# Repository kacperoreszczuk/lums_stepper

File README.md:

# lums_stepper
LUMS Stepper - universal 3-axis stepper motor controller. See lums_stepper.pdf for instructions and more information.

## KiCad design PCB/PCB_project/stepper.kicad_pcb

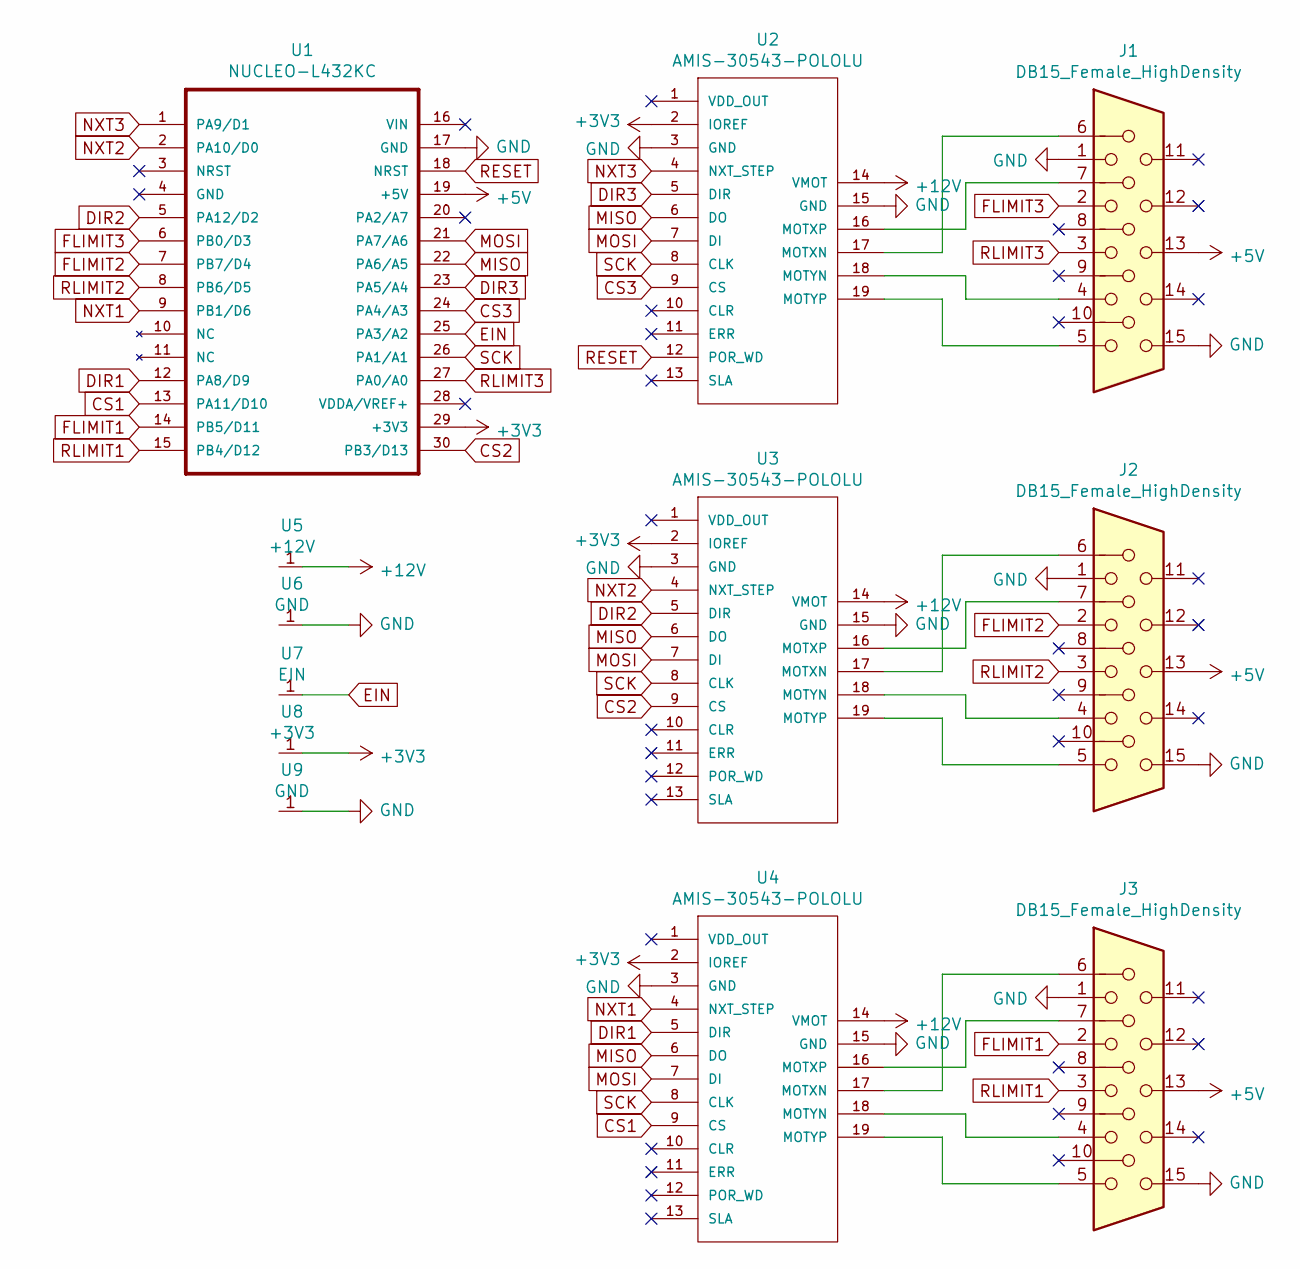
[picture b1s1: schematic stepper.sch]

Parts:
J1, J2, J3: DB15_Female_HighDensity; DSUB-15-HD_Male_Horizontal_Pitch2.29x2.54mm_EdgePinOffset9.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
U1: NUCLEO-L432KC
U2, U3, U4: AMIS-30543-POLOLU
U5: +12V; SolderWirePad_single_2mmDrill
U6: GND; SolderWirePad_single_2mmDrill
U7: EIN; TestPoint_Plated_Hole_D2.0mm
U8: +3V3; TestPoint_Plated_Hole_D2.0mm
U9: GND; TestPoint_Plated_Hole_D2.0mm

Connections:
+3V3: U1.29 (+3V3), U2.2 (IOREF), U3.2 (IOREF), U4.2 (IOREF), U8.1
+5V: J1.13, J2.13, J3.13, U1.19 (+5V)
+12V: U2.14 (VMOT), U3.14 (VMOT), U4.14 (VMOT), U5.1
CS1: U1.13 (PA11/D10), U4.9 (CS)
CS2: U1.30 (PB3/D13), U3.9 (CS)
CS3: U1.24 (PA4/A3), U2.9 (CS)
DIR1: U1.12 (PA8/D9), U4.5 (DIR)
DIR2: U1.5 (PA12/D2), U3.5 (DIR)
DIR3: U1.23 (PA5/A4), U2.5 (DIR)
EIN: U1.25 (PA3/A2), U7.1
FLIMIT1: J3.2, U1.14 (PB5/D11)
FLIMIT2: J2.2, U1.7 (PB7/D4)
FLIMIT3: J1.2, U1.6 (PB0/D3)
GND: J1.1, J1.15, J2.1, J2.15, J3.1, J3.15, U1.17 (GND), U2.3 (GND), U2.15 (GND), U3.3 (GND), U3.15 (GND), U4.3 (GND), U4.15 (GND), U6.1, U9.1
MISO: U1.22 (PA6/A5), U2.6 (DO), U3.6 (DO), U4.6 (DO)
MOSI: U1.21 (PA7/A6), U2.7 (DI), U3.7 (DI), U4.7 (DI)
NXT1: U1.9 (PB1/D6), U4.4 (NXT_STEP)
NXT2: U1.2 (PA10/D0), U3.4 (NXT_STEP)
NXT3: U1.1 (PA9/D1), U2.4 (NXT_STEP)
unnamed: J1.4, U2.18 (MOTYN)
unnamed: J1.5, U2.19 (MOTYP)
unnamed: J1.6, U2.17 (MOTXN)
unnamed: J1.7, U2.16 (MOTXP)
unnamed: J2.4, U3.18 (MOTYN)
unnamed: J2.5, U3.19 (MOTYP)
unnamed: J2.6, U3.17 (MOTXN)
unnamed: J2.7, U3.16 (MOTXP)
unnamed: J3.4, U4.18 (MOTYN)
unnamed: J3.5, U4.19 (MOTYP)
unnamed: J3.6, U4.17 (MOTXN)
unnamed: J3.7, U4.16 (MOTXP)
RESET: U1.18 (NRST), U2.12 (POR_WD)
RLIMIT1: J3.3, U1.15 (PB4/D12)
RLIMIT2: J2.3, U1.8 (PB6/D5)
RLIMIT3: J1.3, U1.27 (PA0/A0)
SCK: U1.26 (PA1/A1), U2.8 (CLK), U3.8 (CLK), U4.8 (CLK)

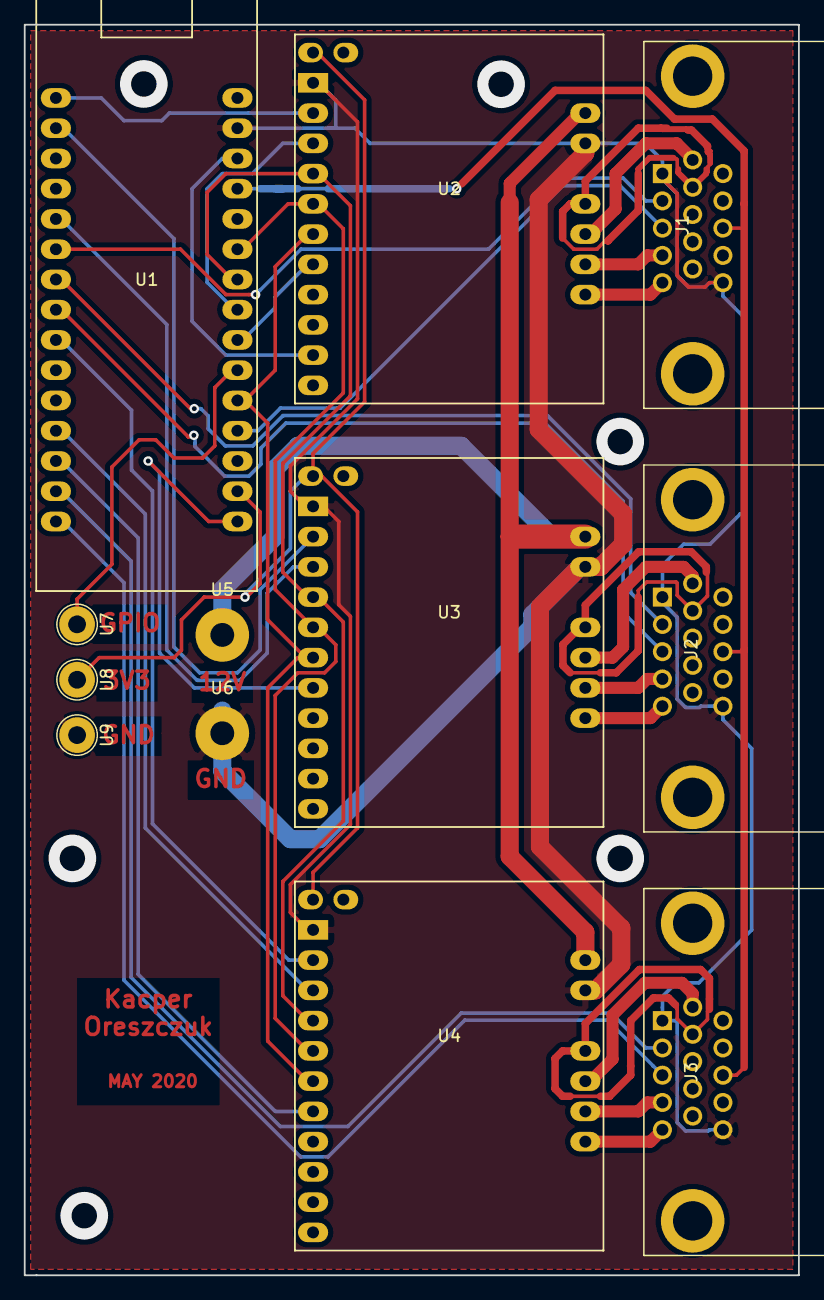
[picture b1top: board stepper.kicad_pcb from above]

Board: 2 copper layers, 65.0 x 105.0 mm, 12 parts (0 on the bottom side), 36 nets.

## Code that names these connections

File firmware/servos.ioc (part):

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Mcu.Name=STM32L432K(B-C)Ux
Mcu.Package=UFQFPN32
Mcu.UserName=STM32L432KCUx
PA0.GPIOParameters=GPIO_PuPd,GPIO_Label
PA0.GPIO_Label=RLIMIT3
PA0.GPIO_PuPd=GPIO_NOPULL
PA0.Signal=GPIO_Input
PA1.Mode=Full_Duplex_Master
PA1.Signal=SPI1_SCK
PA10.GPIOParameters=GPIO_Speed,GPIO_Label
PA10.GPIO_Label=NXT2
PA10.GPIO_Speed=GPIO_SPEED_FREQ_LOW
PA10.Signal=GPIO_Output
PA11.GPIOParameters=PinState,GPIO_Label
PA11.GPIO_Label=CS1
PA11.PinState=GPIO_PIN_SET
PA11.Signal=GPIO_Output
PA12.GPIOParameters=GPIO_Label
PA12.GPIO_Label=DIR2
PA12.Signal=GPIO_Output
PA13\ (JTMS-SWDIO).Mode=Serial_Wire
PA13\ (JTMS-SWDIO).Signal=SYS_JTMS-SWDIO
PA14\ (JTCK-SWCLK).Mode=Serial_Wire
PA14\ (JTCK-SWCLK).Signal=SYS_JTCK-SWCLK
PA15\ (JTDI).GPIOParameters=GPIO_Label
PA15\ (JTDI).GPIO_Label=VCP_RX
PA15\ (JTDI).Mode=Asynchronous
PA15\ (JTDI).Signal=USART2_RX
PA2.GPIOParameters=GPIO_Label
PA2.GPIO_Label=VCP_TX
PA2.Mode=Asynchronous
PA2.Signal=USART2_TX
PA3.GPIOParameters=GPIO_Label
PA3.GPIO_Label=EIO
PA3.Signal=GPIO_Output
PA4.GPIOParameters=PinState,GPIO_Label
PA4.GPIO_Label=CS3
PA4.PinState=GPIO_PIN_SET
PA4.Signal=GPIO_Output
PA5.GPIOParameters=GPIO_Label
PA5.GPIO_Label=DIR3
PA5.Signal=GPIO_Output
PA6.Mode=Full_Duplex_Master
PA6.Signal=SPI1_MISO
PA7.Mode=Full_Duplex_Master
PA7.Signal=SPI1_MOSI
PA8.GPIOParameters=GPIO_Label
PA8.GPIO_Label=DIR1
PA8.Signal=GPIO_Output
PA9.GPIOParameters=GPIO_Speed,GPIO_Label
PA9.GPIO_Label=NXT3
PA9.GPIO_Speed=GPIO_SPEED_FREQ_LOW
PA9.Signal=GPIO_Output
PB0.GPIOParameters=GPIO_Label
PB0.GPIO_Label=FLIMIT3
PB0.Signal=GPIO_Input
PB1.GPIOParameters=GPIO_Speed,GPIO_Label
PB1.GPIO_Label=NXT1
PB1.GPIO_Speed=GPIO_SPEED_FREQ_LOW
PB1.Signal=GPIO_Output
PB3\ (JTDO-TRACESWO).GPIOParameters=GPIO_Label
PB3\ (JTDO-TRACESWO).GPIO_Label=CS2
PB3\ (JTDO-TRACESWO).Signal=GPIO_Output
PB4\ (NJTRST).GPIOParameters=GPIO_PuPd,GPIO_Label
PB4\ (NJTRST).GPIO_Label=RLIMIT1
PB4\ (NJTRST).GPIO_PuPd=GPIO_NOPULL
PB4\ (NJTRST).Signal=GPIO_Input
PB5.GPIOParameters=GPIO_PuPd,GPIO_Label
PB5.GPIO_Label=FLIMIT1
PB5.GPIO_PuPd=GPIO_NOPULL
PB5.Signal=GPIO_Input
PB6.GPIOParameters=GPIO_PuPd,GPIO_Label
PB6.GPIO_Label=RLIMIT2
PB6.GPIO_PuPd=GPIO_NOPULL
PB6.Signal=GPIO_Input
PB7.GPIOParameters=GPIO_PuPd,GPIO_Label
PB7.GPIO_Label=FLIMIT2
PB7.GPIO_PuPd=GPIO_NOPULL
PB7.Signal=GPIO_Input
PC14-OSC32_IN\ (PC14).Signal=RCC_OSC32_IN
PC15-OSC32_OUT\ (PC15).Signal=RCC_OSC32_OUT
RCC.HSE_VALUE=8000000
RCC.SYSCLKFreq_VALUE=80000000
RCC.SYSCLKSource=RCC_SYSCLKSOURCE_PLLCLK
board=NUCLEO-L432KC
boardIOC=true

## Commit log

2019-07-04 Init commit
2019-07-04 3D model for case added
2019-07-04 photo added to documentation
2019-09-02 unique ID added
2019-09-23 Support for different limit switches, axis reversing, homing offset, code refactoring and optimisation, pin swap (not updated in PCB project!!).
2019-10-06 Non-blocking UART TX and real time RX parsing. NXT pin cloning to external output. Bugfix for homing for rotational stages.
2020-02-18 Firmware update - software filtering of limit switches
2020-02-18 updated case model files
2020-02-18 typos in docs
2020-02-18 PCP updated after pin swap
2020-07-30 Adaptatations in pinout for future switch panel
2021-11-01 Added acknowledgements
2021-11-01 Readme now redirects to the pdf with information and instructions
2022-08-08 Homing now possible also to the front limit switch. Change in id encoding in preparation to automatic preparation of binaries for different nodes
2022-08-08 script for generating binaries for multiple nodes at once
2023-01-17 fixed slightly wrong time step constant causing 2% incorrect speed/time calibration
2023-04-30 fixed missing references in pdf documentation
